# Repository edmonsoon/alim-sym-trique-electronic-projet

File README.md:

# alim-sym-trique-electronic-projet
ceci est un projet d'alimentation symétrique en electronique pour donc sans code

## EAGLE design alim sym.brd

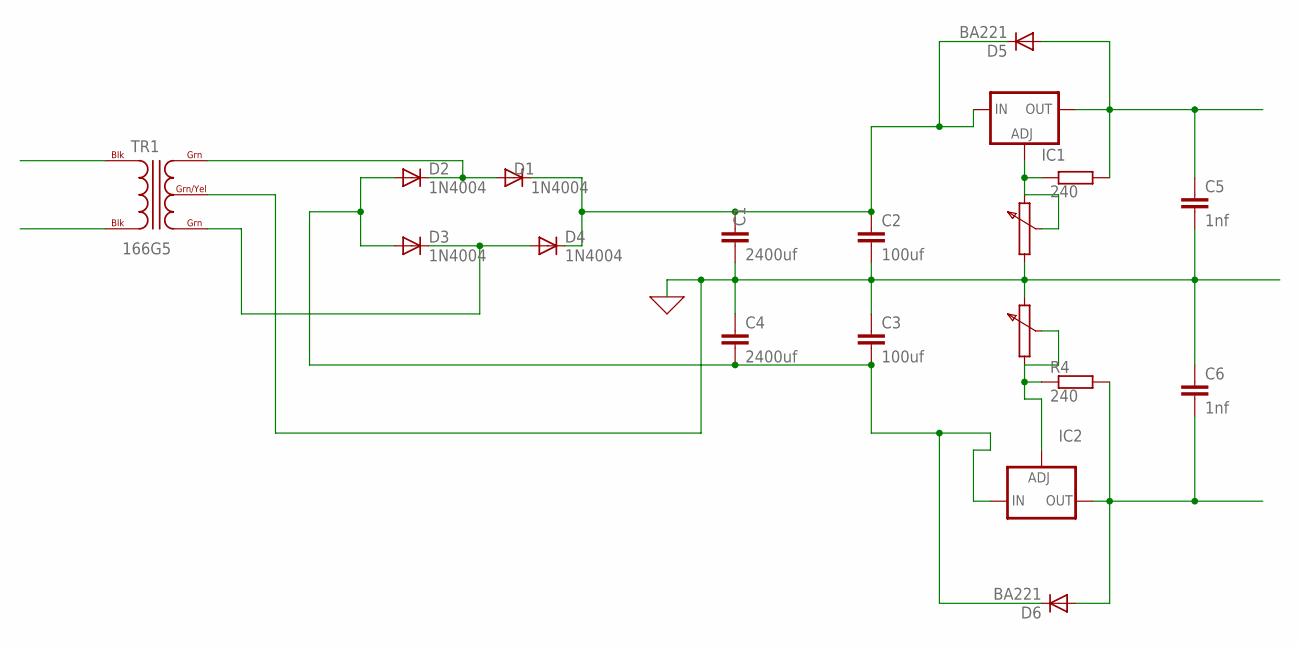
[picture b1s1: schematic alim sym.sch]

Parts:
C1, C4: 2400uf; C2.5-3
C2, C3: 100uf; C2.5-3
C5, C6: 1nf; C2.5-3
D1, D2, D3, D4: 1N4004; DO41-10
D5, D6: BA221; DO35-10
IC1: LM317TS; 317TS
IC2: LM337TS; 337TS
R3, R4: 240; SMS-0
TR1: 166G5; C3H

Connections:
0: C1.2, C2.2, C3.1, C4.1, C5.2, C6.1, TR1.GRN/YEL
unnamed: D1.A, D2.C, TR1.GRN@1 (GRN)
unnamed: D3.C, D4.A, TR1.GRN@2 (GRN)
unnamed: C1.1, C2.1, D1.C, D4.C, D5.C, IC1.3 (IN)
unnamed: IC2.1 (ADJ), R4.2
unnamed: IC1.1 (ADJ), R3.2
unnamed: C3.2, C4.2, D2.A, D3.A, D6.C, IC2.2 (IN)
unnamed: C6.2, D6.A, IC2.3 (OUT), R4.1
unnamed: C5.1, D5.A, IC1.2 (OUT), R3.1

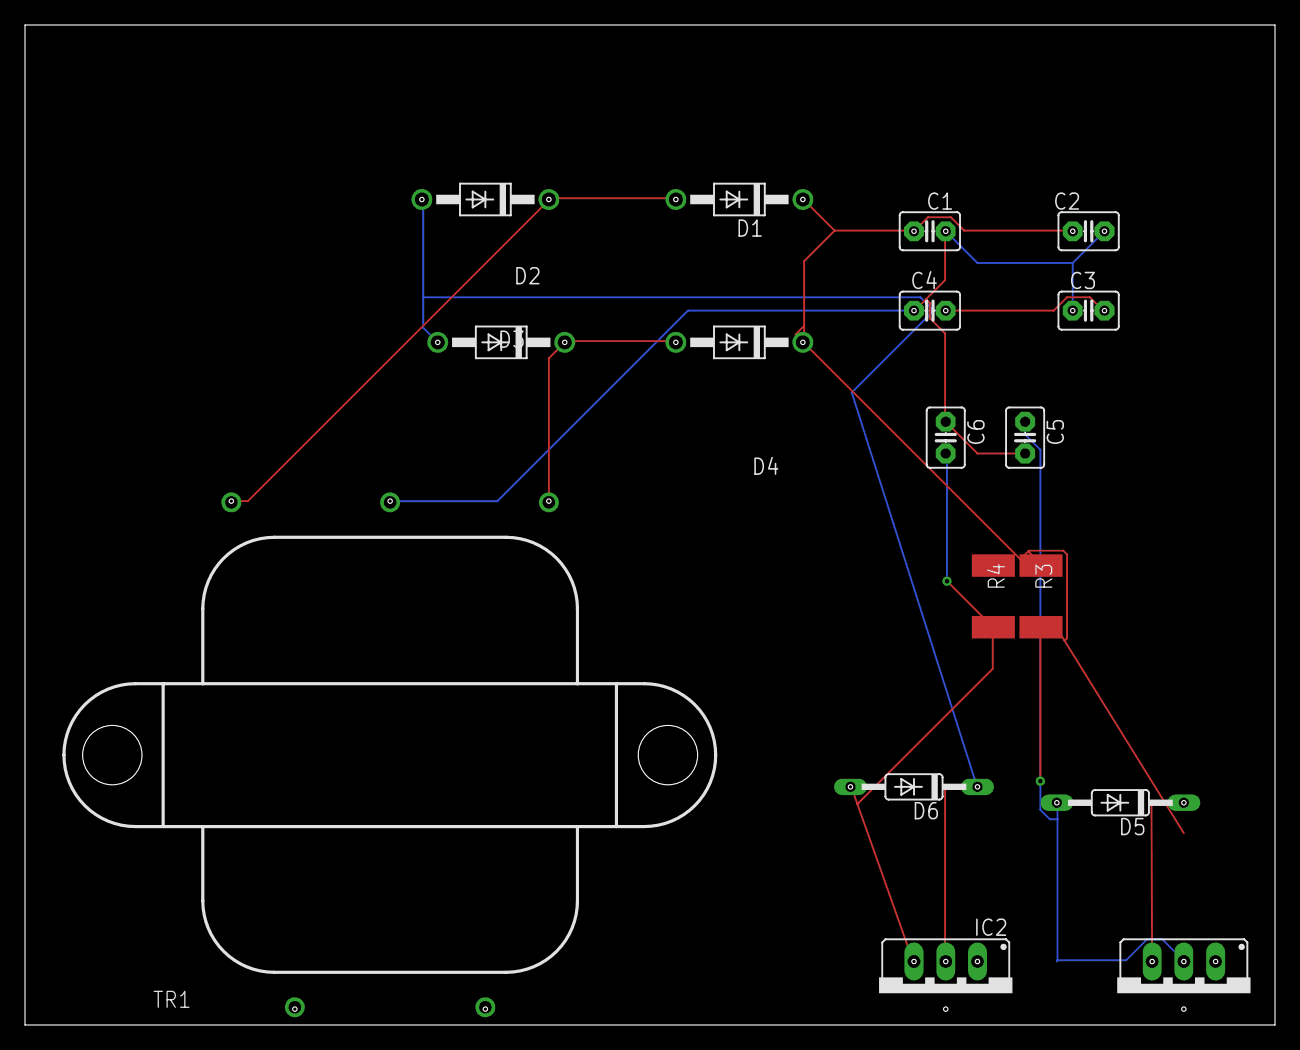
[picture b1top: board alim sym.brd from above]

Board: 2 copper layers, 100.0 x 80.0 mm, 17 parts (0 on the bottom side), 9 nets.
